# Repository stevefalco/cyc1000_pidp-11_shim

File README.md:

# cyc1000 pidp-11 shim
This shim allows a PDP-2011 CYC1000 FPGA implementation of the PDP-11 to be used with a PiDP-11 panel.

The PDP2011 FPGA is described here:  https://pdp2011.sytse.net/wordpress/pdp-11/fpga-boards/cyc1000/

The PiDP-11 is described here:  https://obsolescence.wixsite.com/obsolescence/pidp-11

This shim PCB is viewed from the top.  It directly plugs onto the back of the PiDP-11 PCB.  I designed this shim because I had electrical noise problems that caused Ethernet glitches.  I traced the problem to the cables between the CYC1000 and the Digilent Ethernet and SD modules.  This shim eliminates the cables and allows the Digilent modules to connect directly to the shim PCB.

Here are two views of the assembled PCB, showing the Digilent modules extending vertically from the PCB.

J11 must be installed on the bottom of this PCB in order to properly mate with the PiDP-11.  The CYC1000 and all other parts are installed on the top of this PCB.

All capacitors are optional.  I personally prefer to include them.  For C1, the square pad is the positive terminal and the round pad is the negative terminal.

R1 is optional, but according to the Microchip data sheet for the ENC424J600 (see figure 2-9) it really should be installed.

You can only install J1 (FTDI-Friend) or J12 (RS232 PMOD), not both, to avoid conflicts driving the RX1 signal.  In the photos above I installed the FTDI-Friend.

I also designed a housing, suitable for 3D printing, to fit over the modules, since they are of different heights, and they extend through the back panel of the PiDP-11.  The housing named "cover_ftdi_friend.stl" assumes that you will be using an FTDI Friend rather than an RS232 PMOD.  I removed the female connector from the FTDI Friend, and added a right-angle header, so it could directly solder into the shim.  You will have to modify the housing if you do anything different.  You will find the FreeCAD design file and STL in the housing directory.  Here is a photo:

There is also a housing named "cover_rs232.stl" which can be used with an RS-232 Digilent PMOD in place of the FTDI friend, if you prefer that interface.

A few last details.  I am using an external power supply rather than powering the unit over USB.  While the CYC1000 allows simultaneous USB and external power - it automatically chooses the higher voltage - I didn't want that, so I modified a bulkhead cable by grinding off the rubber shell at the male end, then cutting the red (+5 volt) connection, and applying epoxy for mechanical strength.  Here is a photo of the modified cable:

And finally, this shim connects the FPGA reset signal to the Pi connector on GPIO19, which has a convenient trace on the PiDP-11 PCB.  In the photos you can see a red/white pair of wires; these connect from GPIO19 to the Key Switch of the front panel.  Thus, the Key Switch can be used to hard-reset the FPGA.

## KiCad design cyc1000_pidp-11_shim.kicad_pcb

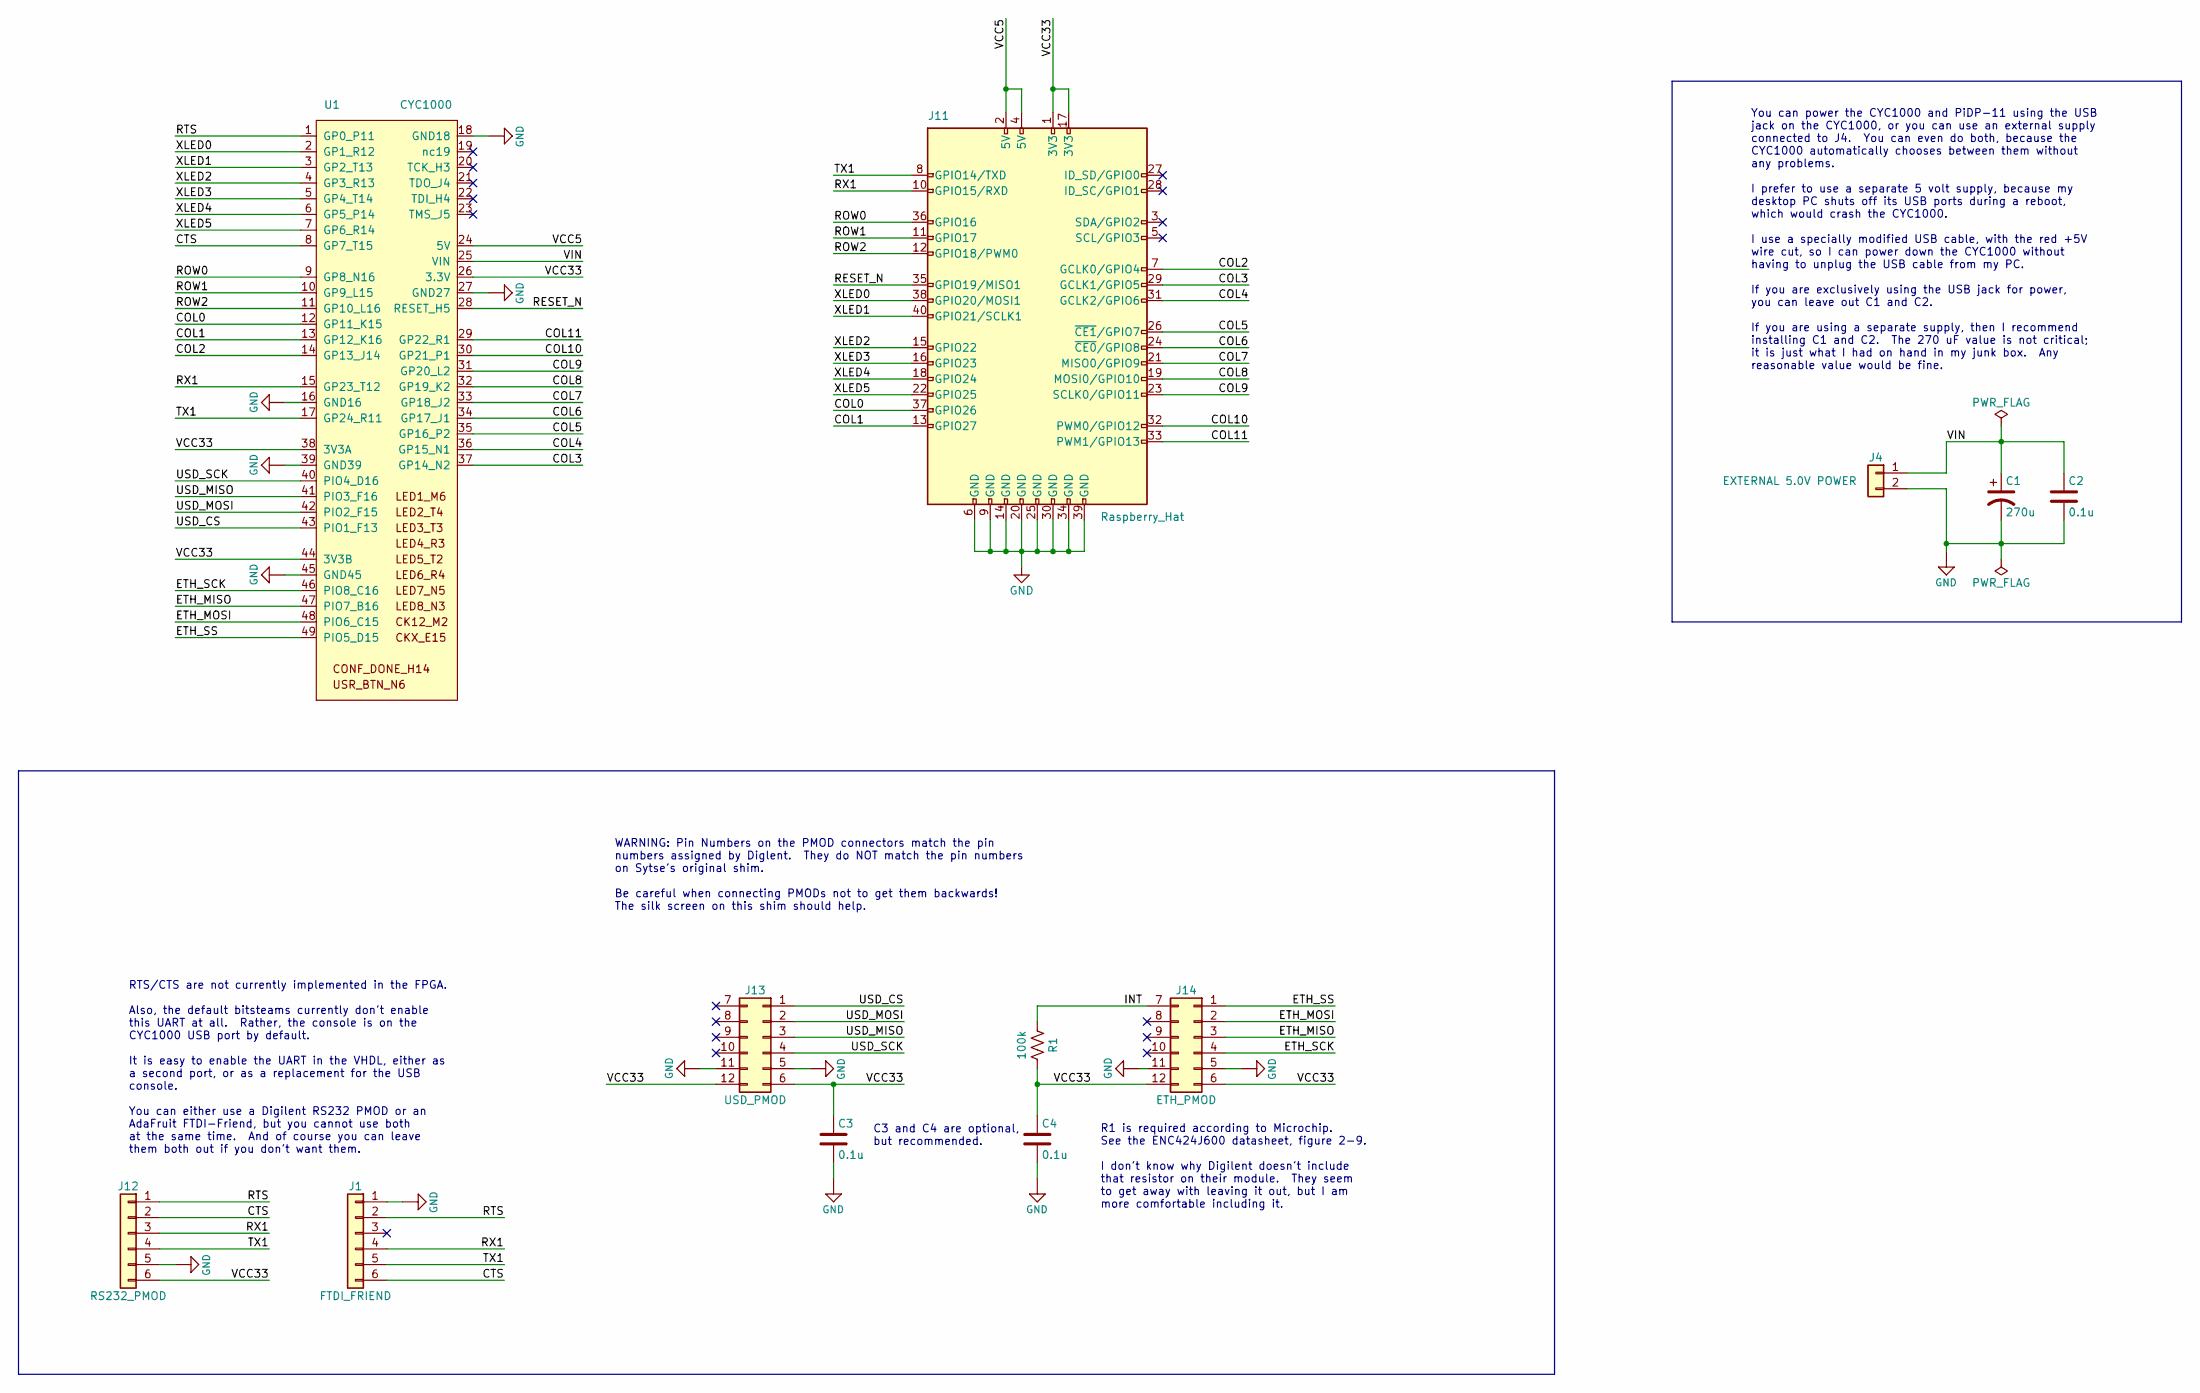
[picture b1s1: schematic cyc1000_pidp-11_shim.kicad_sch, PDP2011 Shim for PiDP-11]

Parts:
C1: 270u; CP_Radial_D10.0mm_P5.00mm
C2, C3, C4: 0.1u; C_Disc_D5.0mm_W2.5mm_P5.00mm
J1: FTDI_FRIEND; ftdi-friend-1x6
J4: EXTERNAL 5.0V POWER; PinHeader_1x02_P2.54mm_Vertical
J11: Raspberry_Hat; PinHeader_2x20_P2.54mm_Vertical
J12: RS232_PMOD; rs232-1x6
J13: USD_PMOD; uSD-2x6
J14: ETH_PMOD; ethernet-2x6
R1: 100k; R_Axial_DIN0207_L6.3mm_D2.5mm_P7.62mm_Horizontal
U1: CYC1000

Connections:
/COL0: J11.37 (GPIO26), U1.12 (GP11_K15)
/COL1: J11.13 (GPIO27), U1.13 (GP12_K16)
/COL2: J11.7 (GCLK0/GPIO4), U1.14 (GP13_J14)
/COL3: J11.29 (GCLK1/GPIO5), U1.37 (GP14_N2)
/COL4: J11.31 (GCLK2/GPIO6), U1.36 (GP15_N1)
/COL5: J11.26 (~CE1/GPIO7), U1.35 (GP16_P2)
/COL6: J11.24 (~CE0/GPIO8), U1.34 (GP17_J1)
/COL7: J11.21 (MISO0/GPIO9), U1.33 (GP18_J2)
/COL8: J11.19 (MOSI0/GPIO10), U1.32 (GP19_K2)
/COL9: J11.23 (SCLK0/GPIO11), U1.31 (GP20_L2)
/COL10: J11.32 (PWM0/GPIO12), U1.30 (GP21_P1)
/COL11: J11.33 (PWM1/GPIO13), U1.29 (GP22_R1)
/CTS: J1.6, J12.2, U1.8 (GP7_T15)
/ETH_MISO: J14.3, U1.47 (PIO7_B16)
/ETH_MOSI: J14.2, U1.48 (PIO6_C15)
/ETH_SCK: J14.4, U1.46 (PIO8_C16)
/ETH_SS: J14.1, U1.49 (PIO5_D15)
/INT: J14.7, R1.1
/RESET_N: J11.35 (GPIO19/MISO1), U1.28 (RESET_H5)
/ROW0: J11.36 (GPIO16), U1.9 (GP8_N16)
/ROW1: J11.11 (GPIO17), U1.10 (GP9_L15)
/ROW2: J11.12 (GPIO18/PWM0), U1.11 (GP10_L16)
/RTS: J1.2, J12.1, U1.1 (GP0_P11)
/RX1: J1.4, J11.10 (GPIO15/RXD), J12.3, U1.15 (GP23_T12)
/TX1: J1.5, J11.8 (GPIO14/TXD), J12.4, U1.17 (GP24_R11)
/USD_CS: J13.1, U1.43 (PIO1_F13)
/USD_MISO: J13.3, U1.41 (PIO3_F16)
/USD_MOSI: J13.2, U1.42 (PIO2_F15)
/USD_SCK: J13.4, U1.40 (PIO4_D16)
/VCC5: J11.2 (5V), J11.4 (5V), U1.24 (5V)
/VCC33: C3.1, C4.1, J11.1 (3V3), J11.17 (3V3), J12.6, J13.6, J13.12, J14.6, J14.12, R1.2, U1.26 (3.3V), U1.38 (3V3A), U1.44 (3V3B)
/VIN: C1.1, C2.1, J4.1, U1.25 (VIN)
/XLED0: J11.38 (GPIO20/MOSI1), U1.2 (GP1_R12)
/XLED1: J11.40 (GPIO21/SCLK1), U1.3 (GP2_T13)
/XLED2: J11.15 (GPIO22), U1.4 (GP3_R13)
/XLED3: J11.16 (GPIO23), U1.5 (GP4_T14)
/XLED4: J11.18 (GPIO24), U1.6 (GP5_P14)
/XLED5: J11.22 (GPIO25), U1.7 (GP6_R14)
GND: C1.2, C2.2, C3.2, C4.2, J1.1, J4.2, J11.6 (GND), J11.9 (GND), J11.14 (GND), J11.20 (GND), J11.25 (GND), J11.30 (GND), J11.34 (GND), J11.39 (GND), J12.5, J13.5, J13.11, J14.5, J14.11, U1.16 (GND16), U1.18 (GND18), U1.27 (GND27), U1.39 (GND39), U1.45 (GND45)

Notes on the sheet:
You can power the CYC1000 and PiDP-11 using the USB jack on the CYC1000, or you can use an external supply connected to J4. You can even do both, because the CYC1000 automatically chooses between them without any problems. I prefer to use a separate 5 volt supply, because my desktop PC shuts off it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
WARNING: Pin Numbers on the PMOD connectors match the pin numbers assigned by Diglent. They do NOT match the pin numbers on Sytse's original shim. Be careful when connecting PMODs not to get them backwards! The silk screen on this shim should help.
C3 and C4 are optional, but recommended.
RTS/CTS are not currently implemented in the FPGA. Also, the default bitsteams currently don't enable this UART at all. Rather, the console is on the CYC1000 USB port by default. It is easy to enable the UART in the VHDL, either as a second port, or as a replacement for the USB console. You can eit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
R1 is required according to Microchip. See the ENC424J600 datasheet, figure 2-9. I don't know why Digilent doesn't include that resistor on their module. They seem to get away with leaving it out, but I am more comfortable including it.

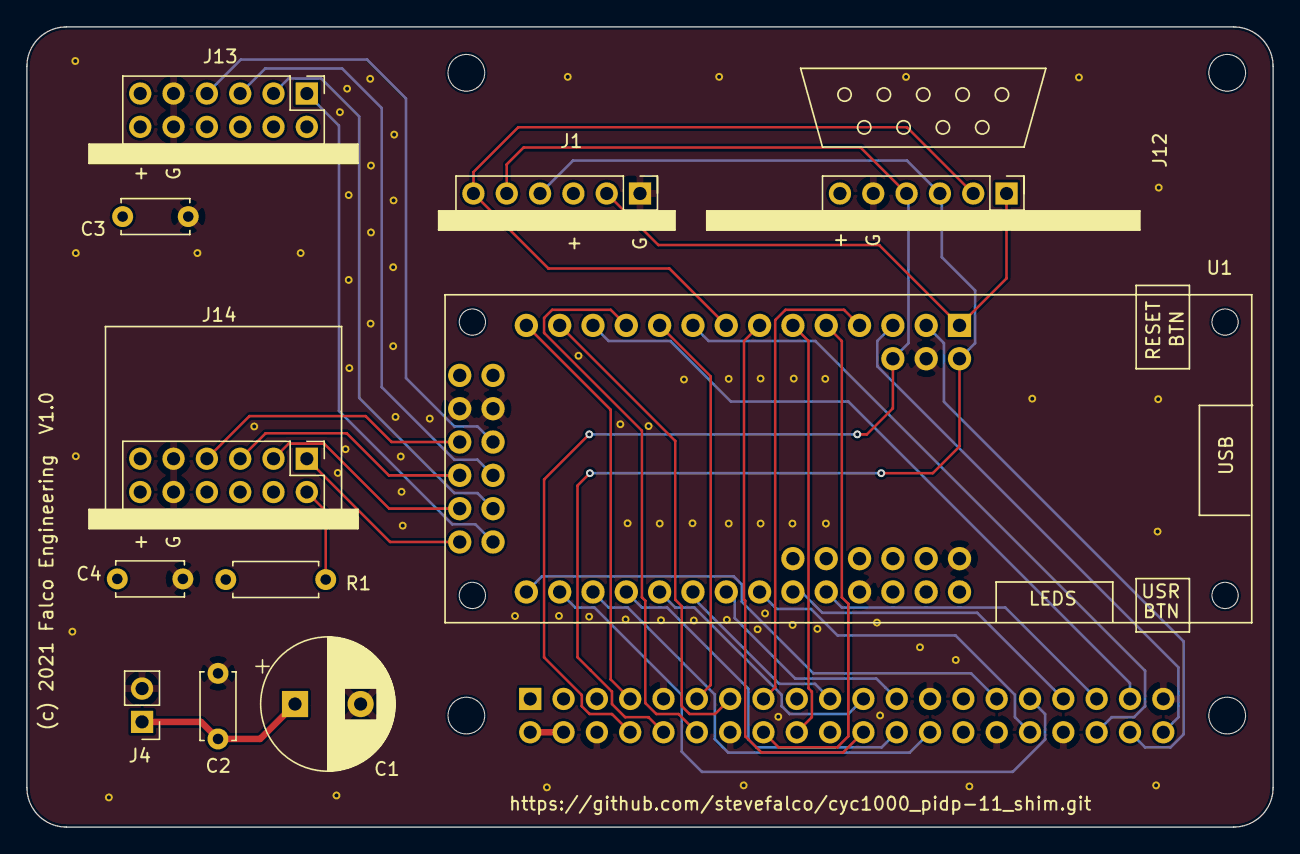
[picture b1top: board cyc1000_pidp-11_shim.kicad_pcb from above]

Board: 4 copper layers, 95.0 x 61.0 mm, 16 parts (1 on the bottom side), 39 nets.

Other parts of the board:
MK1, MK2, MK3, MK4: M2.5; MountingHole_2.7mm_M2.5

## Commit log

2021-01-30 Initial
2021-01-30 Generate gerbers
2021-01-30 Add license and README
2021-01-30 Fix README
2021-01-30 Remove extra caps, add comments
2021-01-30 Ready for manufacture of prototype
2021-02-14 Add housing
2021-02-14 Enlarge holes slightly
2021-02-14 Regenerate gerbers
2021-02-14 Add photos of the finished product
2021-02-16 New housing, more modifyable
2021-02-16 Update README.
2021-02-16 Improved fit of FTDI Friend
2021-03-15 Begin alternate cover for RS232 PMOD
2021-03-16 Fixed basic geometry
2021-03-16 Ready to test
2021-03-16 Tweak position rs232
2021-03-17 Add proper cover for RS232 PMOD
2021-03-17 Add the new housing to the readme
2021-11-21 Convert to KiCad 6
2021-11-24 Move to KiCad 6

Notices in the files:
cyc1000_pidp-11_shim.kicad_pcb:
(c) 2021 Falco Engineering  V1.0
